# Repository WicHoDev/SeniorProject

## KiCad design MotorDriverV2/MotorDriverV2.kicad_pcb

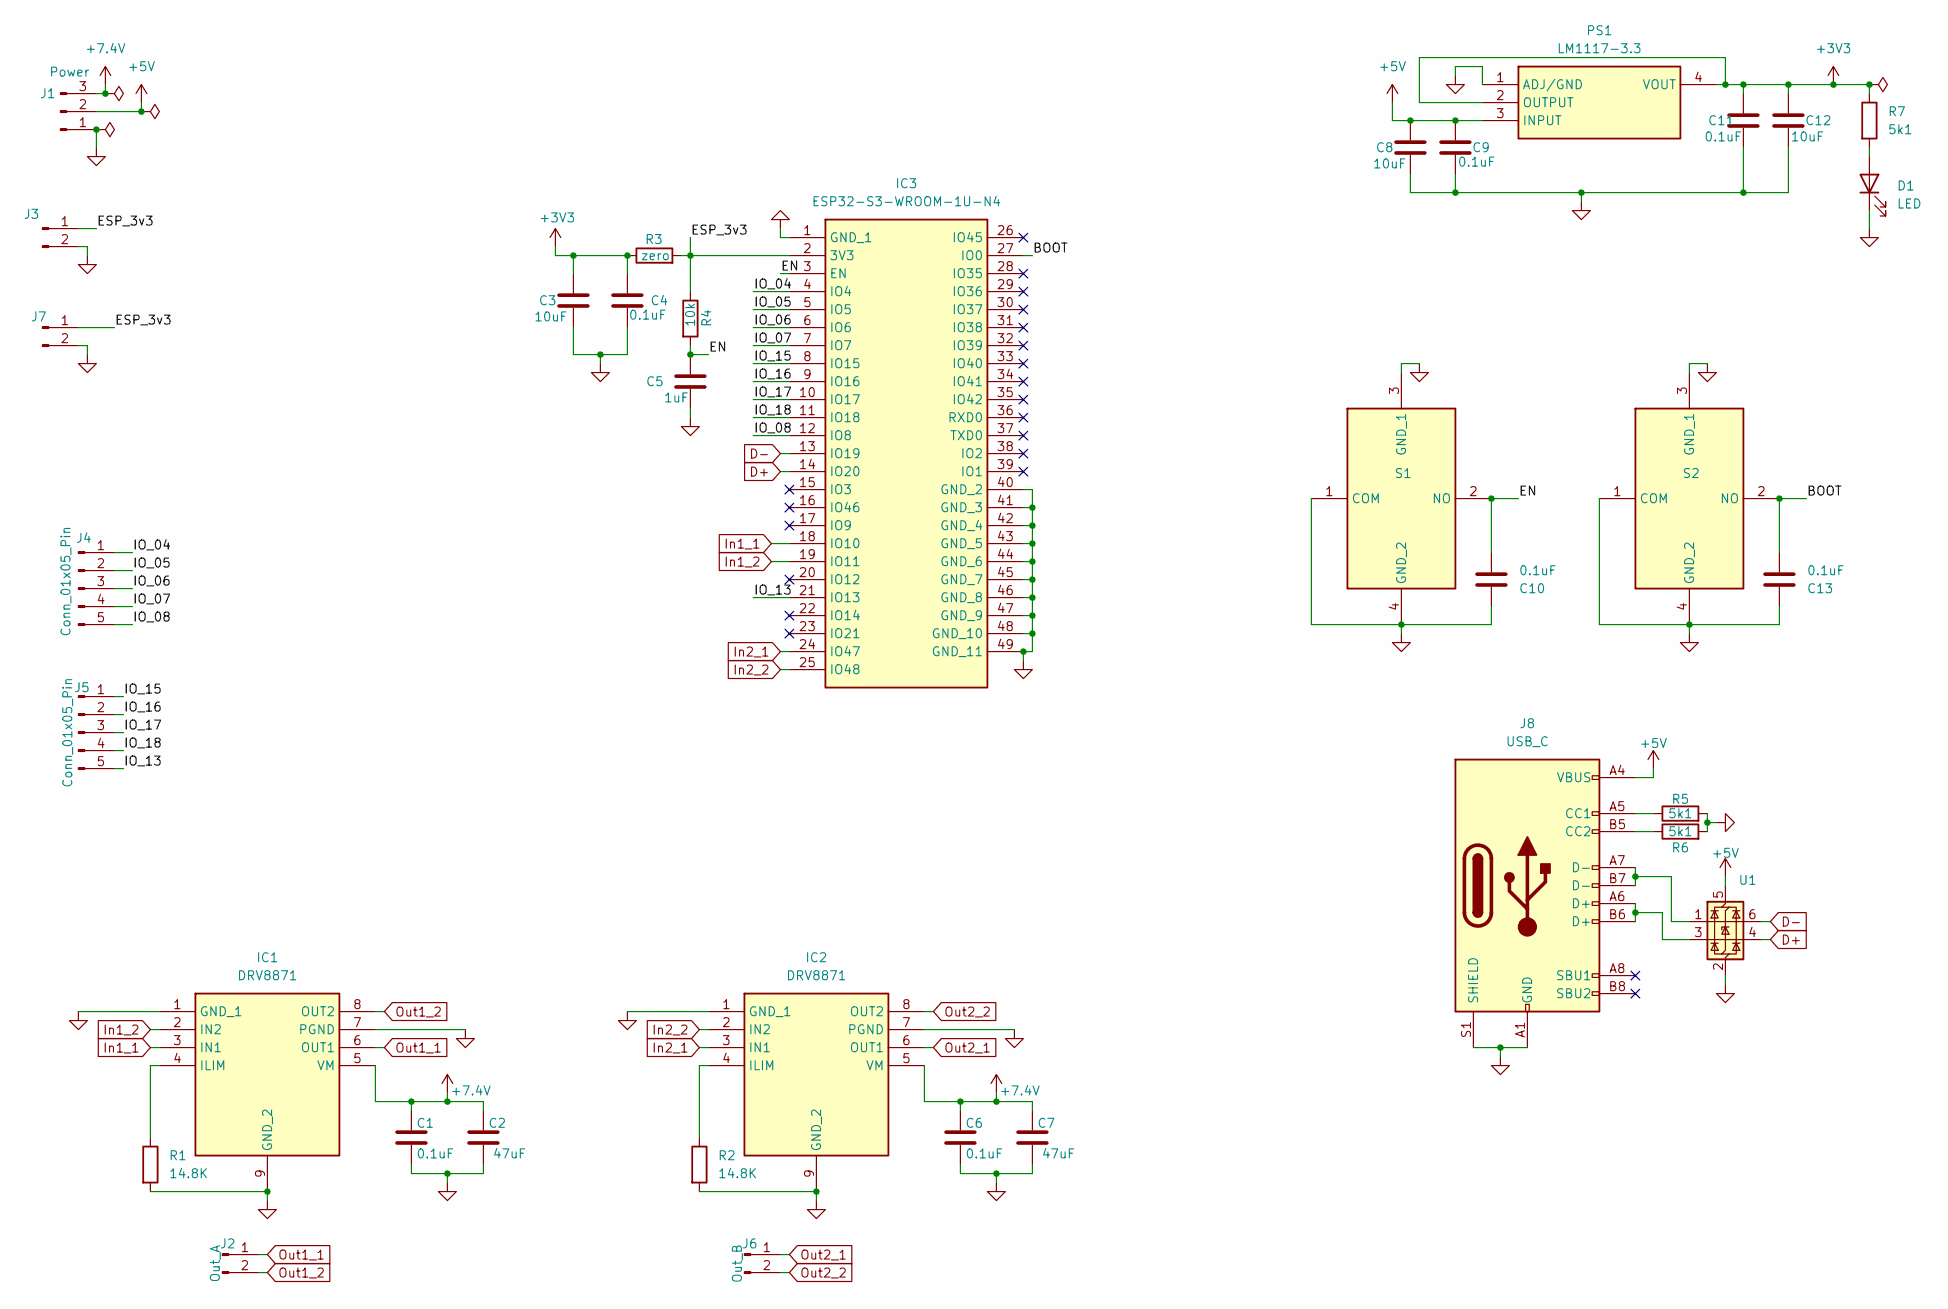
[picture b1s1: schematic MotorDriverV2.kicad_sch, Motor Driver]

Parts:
C1, C4, C6, C9, C10, C11, C13: 0.1uF; C_0805_2012Metric_Pad1.18x1.45mm_HandSolder
C2, C7: 47uF; C_0805_2012Metric_Pad1.18x1.45mm_HandSolder
C3, C8, C12: 10uF; C_0805_2012Metric_Pad1.18x1.45mm_HandSolder
C5: 1uF; C_0805_2012Metric_Pad1.18x1.45mm_HandSolder
D1: LED; LED_0805_2012Metric_Pad1.15x1.40mm_HandSolder
IC1, IC2: DRV8871; SOIC127P600X170-9N; Mouser Part Number 595-DRV8871DDARQ1
IC3: ESP32-S3-WROOM-1U-N4; ESP32S3WROOM1UN4; Mouser Part Number 356-ESP32S3WROOM1UN4
J1: Power; PinHeader_1x03_P2.00mm_Vertical
J2: Out_A; JST_XH_B2B-XH-A_1x02_P2.50mm_Vertical
J3, J7: Conn_01x02_Pin; PinHeader_1x02_P2.54mm_Vertical
J4, J5: Conn_01x05_Pin; PinHeader_1x05_P2.54mm_Vertical
J6: Out_B; JST_XH_B2B-XH-A_1x02_P2.50mm_Vertical
J8: USB_C; USB_C_Receptacle_GCT_USB4105-xx-A_16P_TopMnt_Horizontal
PS1: LM1117-3.3; SOT230P700X180-4N; Mouser Part Number 926-LM1117IMPX33NOPB
R1, R2: 14.8K; R_0805_2012Metric_Pad1.20x1.40mm_HandSolder
R3: zero; R_0805_2012Metric_Pad1.20x1.40mm_HandSolder
R4: 10k; R_0805_2012Metric_Pad1.20x1.40mm_HandSolder
R5, R6, R7: 5k1; R_0805_2012Metric_Pad1.20x1.40mm_HandSolder
S1, S2: PTS636SKG25JSMTR_LFS; PTS636SKG25JSMTRLFS; Mouser Part Number 611-PTS636SKG25JSMTR
U1: USBLC6-2SC6; SOT-23-6

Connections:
+3V3: C3.1, C4.1, C11.1, C12.1, PS1.2 (OUTPUT), PS1.4 (VOUT), R3.1, R7.1
+5V: C8.1, C9.1, J1.2, J8.A4 (VBUS), J8.A9 (VBUS), J8.B4 (VBUS), J8.B9 (VBUS), PS1.3 (INPUT), U1.5 (VBUS)
+7.4V: C1.1, C2.1, C6.1, C7.1, IC1.5 (VM), IC2.5 (VM), J1.3
/BOOT: C13.2, IC3.27 (IO0), S2.2 (NO)
/EN: C5.1, C10.2, IC3.3 (EN), R4.2, S1.2 (NO)
/ESP_3v3: IC3.2 (3V3), J3.1, J7.1, R3.2, R4.1
/IO_04: IC3.4 (IO4), J4.1
/IO_05: IC3.5 (IO5), J4.2
/IO_06: IC3.6 (IO6), J4.3
/IO_07: IC3.7 (IO7), J4.4
/IO_08: IC3.12 (IO8), J4.5
/IO_13: IC3.21 (IO13), J5.5
/IO_15: IC3.8 (IO15), J5.1
/IO_16: IC3.9 (IO16), J5.2
/IO_17: IC3.10 (IO17), J5.3
/IO_18: IC3.11 (IO18), J5.4
D+: IC3.14 (IO20), U1.4 (I/O2)
D-: IC3.13 (IO19), U1.6 (I/O1)
GND: C1.2, C2.2, C3.2, C4.2, C5.2, C6.2, C7.2, C8.2, C9.2, C10.1, C11.2, C12.2, C13.1, D1.1 (K), IC1.1 (GND_1), IC1.7 (PGND), IC1.9 (GND_2), IC2.1 (GND_1), IC2.7 (PGND), IC2.9 (GND_2), IC3.1 (GND_1), IC3.40 (GND_2), IC3.41 (GND_3), IC3.42 (GND_4), IC3.43 (GND_5), IC3.44 (GND_6), IC3.45 (GND_7), IC3.46 (GND_8), IC3.47 (GND_9), IC3.48 (GND_10), IC3.49 (GND_11), J1.1, J3.2, J7.2, J8.A1 (GND), J8.A12 (GND), J8.B1 (GND), J8.B12 (GND), J8.S1 (SHIELD), PS1.1 (ADJ/GND), R1.2, R2.2, R5.2, R6.2, S1.1 (COM), S1.3 (GND_1), S1.4 (GND_2), S2.1 (COM), S2.3 (GND_1), S2.4 (GND_2), U1.2 (GND)
In1_1: IC1.3 (IN1), IC3.18 (IO10)
In1_2: IC1.2 (IN2), IC3.19 (IO11)
In2_1: IC2.3 (IN1), IC3.24 (IO47)
In2_2: IC2.2 (IN2), IC3.25 (IO48)
unnamed: D1.2 (A), R7.2
unnamed: IC1.4 (ILIM), R1.1
unnamed: IC2.4 (ILIM), R2.1
unnamed: J8.A5 (CC1), R5.1
unnamed: J8.B5 (CC2), R6.1
unnamed: J8.A6 (D+), J8.B6 (D+), U1.3 (I/O2)
unnamed: J8.A7 (D-), J8.B7 (D-), U1.1 (I/O1)
Out1_1: IC1.6 (OUT1), J2.1
Out1_2: IC1.8 (OUT2), J2.2
Out2_1: IC2.6 (OUT1), J6.1
Out2_2: IC2.8 (OUT2), J6.2

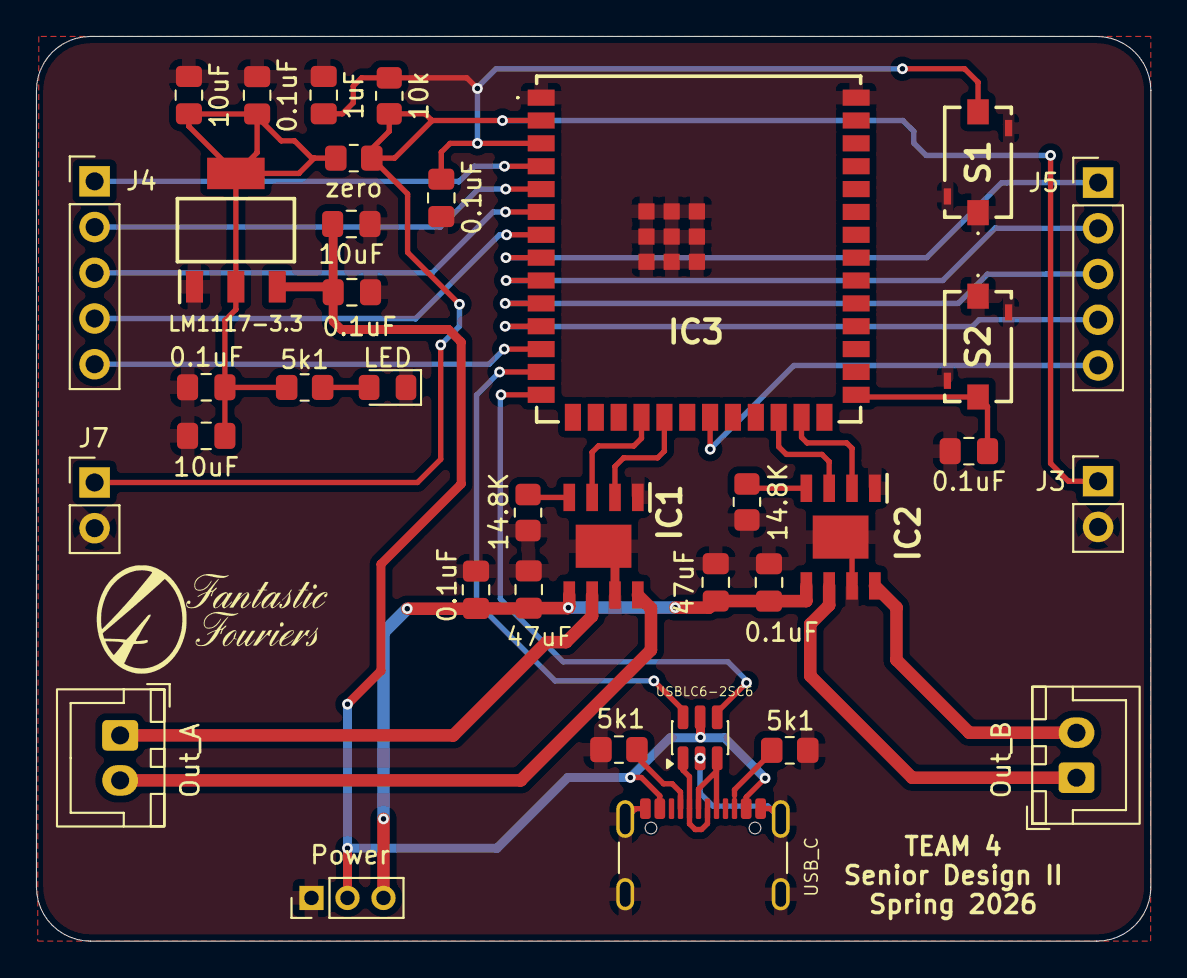
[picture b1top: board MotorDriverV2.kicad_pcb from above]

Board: 2 copper layers, 61.9 x 50.3 mm, 38 parts (1 on the bottom side), 34 nets.

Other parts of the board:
G1, G1#2: LOGO; FFLogo

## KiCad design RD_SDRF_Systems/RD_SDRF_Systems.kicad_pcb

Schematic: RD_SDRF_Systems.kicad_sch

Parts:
C1, C2, C4, C5: 0.1μF; C_0603_1608Metric
C3: 0.33μF; C_0603_1608Metric
C6, C8, C17, C22, C23: 0.01uF; C_0402_1005Metric
C7: 0.47μF; C_0603_1608Metric
C9, C11, C14: 10μF; C_0603_1608Metric
C10: 15nF; C_0603_1608Metric
C12: 10nF; C_0603_1608Metric
C13, C16, C18, C19, C20, C21: 1μF; C_0603_1608Metric
C15: 2.2nF; C_0603_1608Metric
C27, C30, C31, C32, C64, C65, C66, C67, C68, C69, C72, C73, C74, C75, C76: 0.1uF; C_0402_1005Metric
C28, C29: 10pF; C_0402_1005Metric
C33, C34, C36, C37, C81, C82: 100pF; C_0402_1005Metric
C35, C50, C54, C58: 10uF; C_0402_1005Metric
C38, C39, C40, C41, C42, C43, C45, C46, C47, C49, C51, C52, C53, C55, C56, C57, C59, C79, C80: 100nF; C_0402_1005Metric
C44: 2.2uF; C_0402_1005Metric
C48: 1uF; C_0402_1005Metric
C60, C61: 20pF; C_0402_1005Metric
C62, C71: 18pF; C_0402_1005Metric
C63, C70: 4.7uF; C_0402_1005Metric
C77, C78: 10uF; CP_EIA-3528-21_Kemet-B
FB1, FB2, FB3, FB4, FB6, FB7: FerriteBead_Small; L_0402_1005Metric
IC1: ERA-50SM+; ERA50SM; Mouser Part Number 139-ERA-50SM
J1, J2: 132255-11; CONN_132255-11_AMP
J3: FTSH-105-01-L-DV-K; CON10_2X5_DUK_FTSH_SAI
J4: USB_C_Receptacle_USB2.0_16P; USB_C_Receptacle_GCT_USB4105-xx-A_16P_TopMnt_Horizontal
J5: Conn_01x02_Pin; PinHeader_1x02_P2.54mm_Vertical
R1, R2, R3, R4: 10kΩ; R_0402_1005Metric
R5: 330; R_0402_1005Metric
R6, R10: 50; R_0402_1005Metric
R7, R8, R11, R12: 0; R_0402_1005Metric
R9: 30k; R_0402_1005Metric
R13, R14, R15: 10k; R_0402_1005Metric
R16, R17, R21, R22: 100; R_0402_1005Metric
R18: 10; R_0402_1005Metric
R19, R20, R23, R24, R25, R26: 10000; R_0402_1005Metric
R27, R28: 5100; R_0402_1005Metric
R29: 100k; R_0402_1005Metric
R30: 200k; R_0402_1005Metric
R31: 12000; R_0402_1005Metric
R32: 22; R_0402_1005Metric
TR1: TC1-1-13M+; Transformer_MiniCircuits_AT224-1A
U1: LMX2572LPRHAT; IC_LMX2572LPRHAT; PARTREV 08/22/2019
U2: TRF371109IRGZT; RGZ48_5P6X5P6
U3: AD4630-16BBCZ; 05-08-1797_ADI
U4, U5: SN74AXC8T245PWR; PW0024A_N
U6: STM32H723ZGT6; QFP50P2200X2200X160-144N; PARTREV 4
U7: USB3300-EZK-TR; QFN50P500X500X100-33N; DIGI-KEY_PART_NUMBER USB3300-EZK-CT-ND
U8, U9: LM1117MP-1.8; SOT230P700X180-4N
VR1: UA78M33CDCYR; VREG_UA78M33CDCYR; PARTREV T
X1: AK2PAF1-100.00000T; AK2_ABR
Y1: ABM8-25.000MHZ-B2-T; XTAL_ABM8-25.000MHZ-B2-T; PARTREV 44041
Y2: ABM8-24.000MHz-10-B1U-T; XTAL_ABM8-24.000MHz-10-B1U-T; PARTREV 44041

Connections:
+5V: C3.1, C30.2, C31.2, FB1.1, FB2.1, FB3.1, FB4.1, FB7.1, J5.1, R13.1, R14.1, R15.1, R18.1, U2.4 (VCCMIX1), U2.9 (VCCMIX2), U3.A3 (VDD_5V), U3.B3 (VDD_5V), VR1.1 (INPUT)
/1V8: C39.1, C41.1, C63.1, C66.1, C68.1, C70.1, C76.1, C78.2, R19.1, R20.1, U2.24 (VCM), U3.A8 (VIO), U3.B8 (VIO), U3.G3 (VDD_1.8V), U3.H3 (VDD_1.8V), U4.1 (VCCA), U4.2 (DIR), U4.11 (DIR2), U5.1 (VCCA), U7.15 (VDD1.8-1), U7.26 (VDD1.8), U7.29 (VDDA1.8), U9.2 (VOUT__1), U9.4 (VOUT)
/*CS: R20.2, U3.H5 (*CS), U4.5 (A3)
/*RST: R19.2, U3.A7 (*RST), U4.7 (A5)
/AD4630_BUSY: U5.21 (B1), U6.49 (PF11)
/AD4630_CNV: U4.18 (B4), U6.65 (PE12)
/AD4630_CS: U4.19 (B3), U6.64 (PE11)
/AD4630_RST: U4.17 (B5), U6.66 (PE13)
/AD4630_SDO0: U5.20 (B2), U6.50 (PF12)
/AD4630_SDO1: U5.19 (B3), U6.53 (PF13)
/AD4630_SDO2: U5.18 (B4), U6.54 (PF14)
/AD4630_SDO3: U5.17 (B5), U6.55 (PF15)
/BUSY: U3.E8 (BUSY_SCKOUT), U5.3 (A1)
/CNV: U3.A6 (CNV), U4.6 (A4)
/DM: J4.A7 (D-), J4.B7 (D-), U7.8 (DM)
/DP: J4.A6 (D+), J4.B6 (D+), U7.7 (DP)
/I_Channel+: R16.1, U2.34 (BBLOUTP)
/I_Channel-: R17.1, U2.33 (BBLOUTN)
/LMX_CE: U1.1 (CE), U6.4 (PE5)
/LMX_CSB: U1.24 (CSB), U6.35 (PA1)
/LOIN: C6.2, U2.30 (LOIN)
/LOIP: C8.2, U2.31 (LOIP)
/MIXINN: C29.2, U2.7 (MIXINN)
/MIXINP: C28.2, U2.6 (MIXINP)
/OSCINM: C1.1, U1.9 (OSCINM)
/OSCINP: C2.1, U1.8 (OSCINP)
/Q_Channel+: R22.2, U2.28 (BBQOUTP)
/Q_Channel-: R21.2, U2.27 (BBQOUTN)
/RF_MIXIN: C23.1, TR1.6
/RF_MUXout: U1.20 (MUXOUT), U6.36 (PA2)
/SCK: U3.H7 (SCK), U4.3 (A1)
/SDI: U3.H6 (SDI), U4.4 (A2)
/SDO0: U3.D8 (SDO0), U5.7 (A5)
/SDO1: U3.C8 (SDO1), U5.6 (A4)
/SDO2: U3.D7 (SDO2), U5.5 (A3)
/SDO3: U3.C7 (SDO3), U5.4 (A2)
/SPI1_MISO: U6.43 (PA7)
/SPI1_MOSI: U1.17 (SDI), U2.47 (DATA), U4.20 (B2), U6.42 (PA6)
/SPI1_SCK: R32.2, U1.16 (SCK), U2.48 (CLOCK), U4.21 (B1)
/SWO: J3.6, U6.133 (PB3/JTDO/TRACESWO)
/TRF_EN: U2.3 (CHIP_EN), U6.45 (PC5)
/TRF_STROBE: U2.46 (STROBE), U6.40 (PA4)
/ULPI_CLK: U6.100 (PA8), U7.14 (CLKOUT)
/ULPI_D0: U6.37 (PA3), U7.24 (DATA[0])
/ULPI_D1: U6.46 (PB0), U7.23 (DATA[1])
/ULPI_D2: U6.47 (PB1), U7.22 (DATA[2])
/ULPI_D3: U6.69 (PB10), U7.21 (DATA[3])
/ULPI_D4: U6.70 (PB11), U7.20 (DATA[4])
/ULPI_D5: U6.73 (PB12), U7.19 (DATA[5])
/ULPI_D6: U6.74 (PB13), U7.18 (DATA[6])
/ULPI_D7: U6.135 (PB5), U7.17 (DATA[7])
/ULPI_DIR: U6.28 (PC2_C), U7.12 (DIR)
/ULPI_NXT: U6.29 (PC3_C), U7.11 (NXT)
/ULPI_RST: U6.44 (PC4), U7.9 (RESET)
/ULPI_STP: U6.26 (PC0), U7.13 (STP)
/VBUS: J4.A4 (VBUS), J4.A9 (VBUS), J4.B4 (VBUS), J4.B9 (VBUS), R29.2
/nRST: C42.1, J3.8, R23.2, U6.25 (~RST)
unnamed: C10.2, R5.1
unnamed: C17.2, J1.1
unnamed: C22.2, J2.1
unnamed: C28.1, TR1.1
unnamed: C29.1, TR1.3
unnamed: C62.1, Y2.1
unnamed: C23.2, IC1.3 (RF-OUT_AND_DC-IN)
unnamed: C22.1, IC1.1 (RFIN)
unnamed: J4.A5 (CC1), R27.1
unnamed: J4.B5 (CC2), R28.1
unnamed: R10.1, TR1.4
unnamed: R2.1, U1.30 (RAMPCLK)
unnamed: R3.1, U1.32 (RAMPDIR)
unnamed: R6.1, U1.22 (RFOUTAM)
unnamed: C17.1, U1.23 (RFOUTAP)
unnamed: C8.1, U1.18 (RFOUTBM)
unnamed: C6.1, U1.19 (RFOUTBP)
unnamed: R1.1, U1.5 (SYNC)
unnamed: R4.1, U1.28 (SYSREFREQ)
unnamed: C9.1, U1.33 (VBIASVARAC)
unnamed: C5.1, U1.27 (VBIASVCO2)
unnamed: C7.1, U1.3 (VBIASVCO)
unnamed: C11.1, U1.29 (VREFVCO2)
unnamed: C14.1, U1.36 (VREFVCO)
unnamed: C13.1, U1.10 (VREGIN)
unnamed: C12.1, U1.38 (VREGVCO)
unnamed: R13.2, U2.41 (GAIN_B0)
unnamed: R14.2, U2.40 (GAIN_B1)
unnamed: R15.2, U2.39 (GAIN_B2)
unnamed: R12.2, U2.44 (MIXIOUTN)
unnamed: R11.2, U2.45 (MIXOUTP)
unnamed: R8.2, U2.17 (MIXQOUTN)
unnamed: R7.2, U2.16 (MIXQOUTP)
unnamed: R9.2, U2.20 (REXT)
unnamed: C75.1, FB4.2, U2.36 (VCBBI)
unnamed: C73.1, FB2.2, U2.25 (VCCBBQ)
unnamed: C72.1, FB7.2, U2.21 (VCCBIAS)
unnamed: C27.1, FB1.2, U2.2 (VCCDIG)
unnamed: C74.1, FB3.2, U2.29 (VCCLO)
unnamed: C33.1, C81.2, R16.2, U3.B1 (IN0+)
unnamed: C34.1, C81.1, R17.2, U3.C1 (IN0-)
unnamed: C37.1, C82.2, R22.1, U3.F1 (IN1+)
unnamed: C36.1, C82.1, R21.1, U3.G1 (IN1-)
unnamed: C35.1, R18.2, U3.A2 (REFIN)
unnamed: R24.2, U6.138 (BOOT0)
unnamed: R32.1, U6.41 (PA5)
unnamed: J3.2, R25.2, U6.105 (PA13/JTMS/SWDIO)
unnamed: J3.4, R26.1, U6.109 (PA14/JTCK/SWCLK)
unnamed: C47.1, C48.2, FB6.1, U6.32 (VREF+)
unnamed: C60.2, U6.23 (PH0-OSC_IN), Y1.1
unnamed: C61.2, U6.24 (PH1-OSC_OUT), Y1.3
unnamed: R31.1, U7.32 (RBIAS)
unnamed: R29.1, R30.1, U7.4 (VBUS)
unnamed: C62.2, U7.28 (XI)
unnamed: C71.1, U7.27 (XO), Y2.3
unnamed: C1.2, X1.5 (COMPLEMENTARY_OUTPUT)
unnamed: C2.2, X1.4 (OUTPUT)
VCAP: C44.1, U6.71 (VCAP), U6.106 (VCAP)
VCC: C4.1, C16.1, C18.1, C19.1, C20.1, C21.1, C32.2, C38.1, C40.1, C43.2, C45.2, C46.1, C49.2, C50.2, C51.2, C52.1, C53.1, C54.2, C55.2, C56.1, C57.2, C58.2, C59.2, C64.1, C65.1, C67.1, C69.1, C77.1, C79.2, C80.2, FB6.2, J3.1, R23.1, R25.1, U1.7 (VCCDIG), U1.11 (VCCCP), U1.15 (VCCMASH), U1.26 (VCCVCO2), U1.37 (VCCVCO), U4.23 (VCCB), U5.23 (VCCB), U6.6 (VBAT), U6.17 (VDD), U6.30 (VDD), U6.33 (VDDA), U6.39 (VDD), U6.52 (VDD), U6.62 (VDD), U6.72 (VDD), U6.84 (VDD), U6.95 (VDD33USB), U6.108 (VDD), U6.121 (VDD), U6.131 (VDD), U6.143 (PDR_ON), U6.144 (VDD), U7.5 (ID), U7.6 (VDD3.3-3), U7.16 (VDD3.3-2), U7.25 (VDD3.3-1), U7.30 (VDD3.3), U7.31 (REG_EN), U9.3 (VIN), VR1.3 (OUTPUT)

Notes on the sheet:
RF Synthesizer
Oscillator_RF Synth
Analog-to-Digital Converter
Low Noise Amplifier
Level Shifters
USB-C
Balun
Voltage Regulator
10uF capacitors are found https://www.digikey.com/en/models/818691?tab=ultralibrarian
Loop Filter
Down Converter
STM32 MCU

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
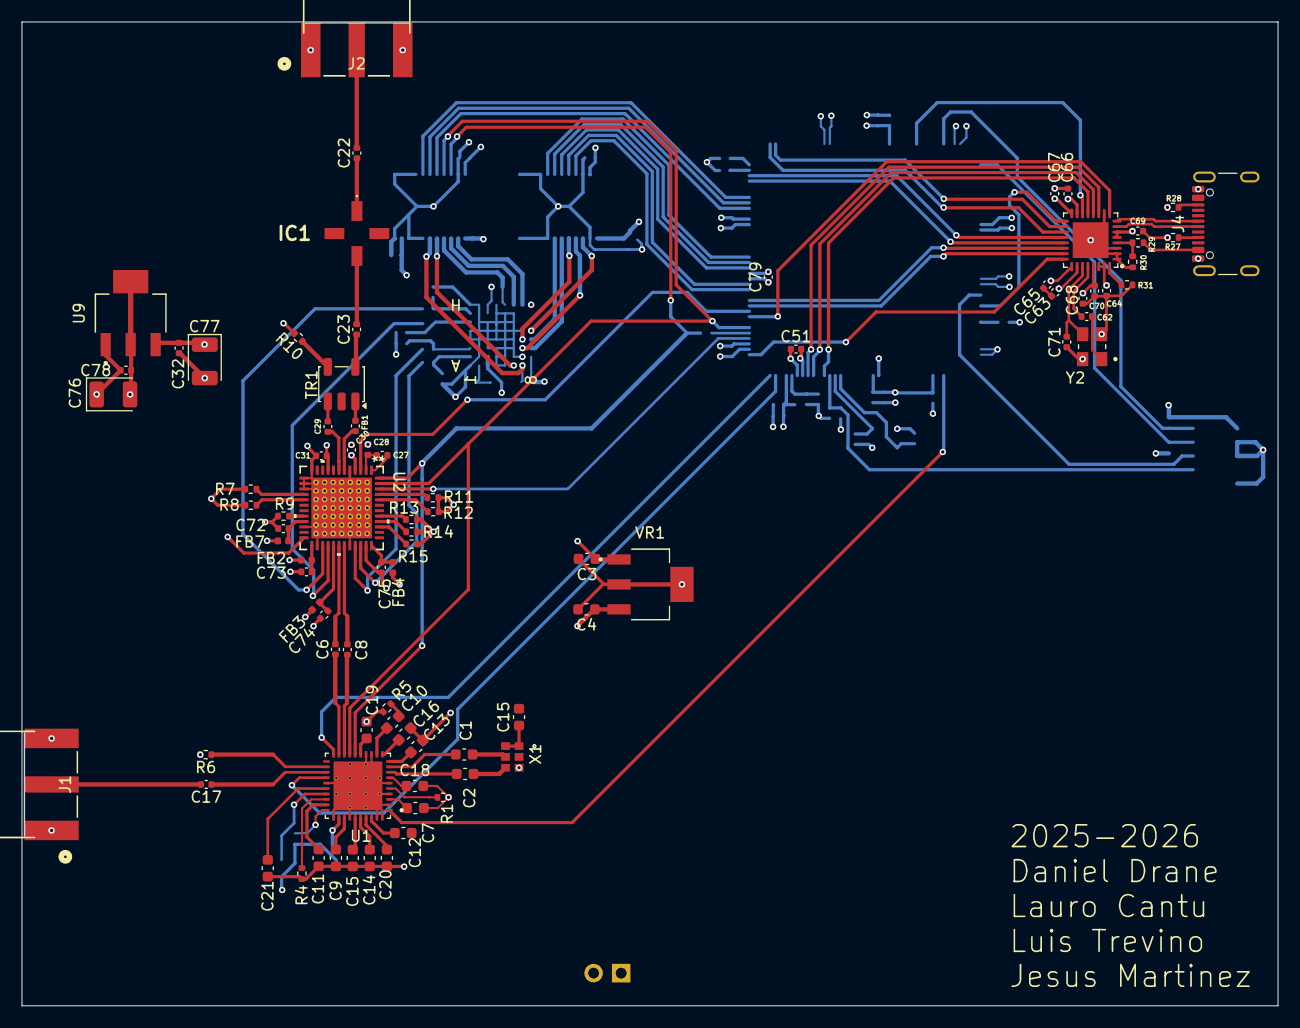
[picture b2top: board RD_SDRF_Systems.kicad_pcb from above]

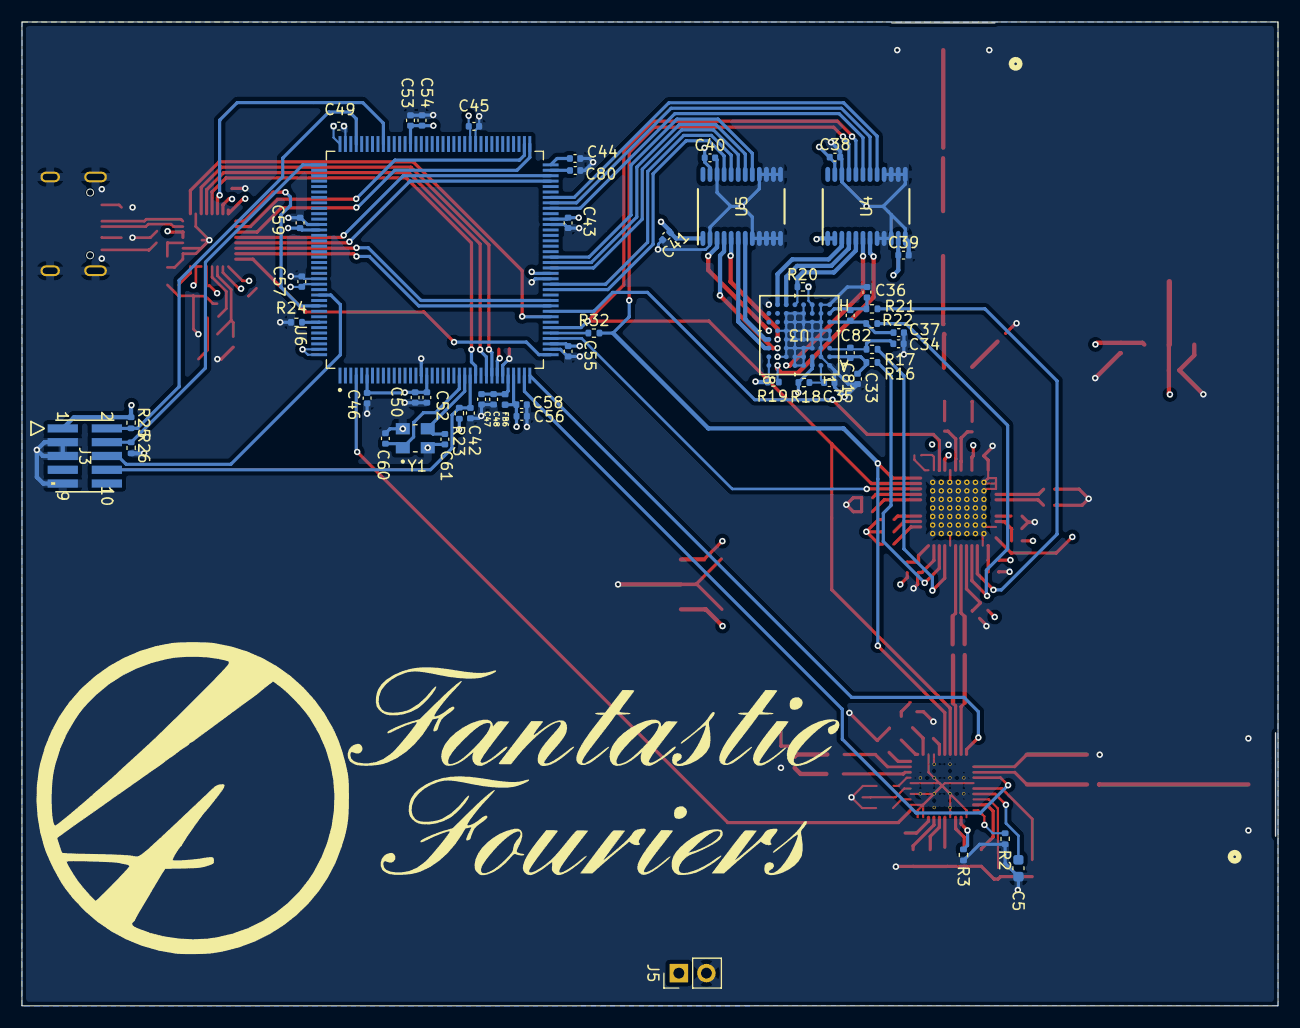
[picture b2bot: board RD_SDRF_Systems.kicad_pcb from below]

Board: 4 copper layers, 115.7 x 90.6 mm, 137 parts (54 on the bottom side), 118 nets.

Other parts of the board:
C15#2: 2.2nF; C_0603_1608Metric

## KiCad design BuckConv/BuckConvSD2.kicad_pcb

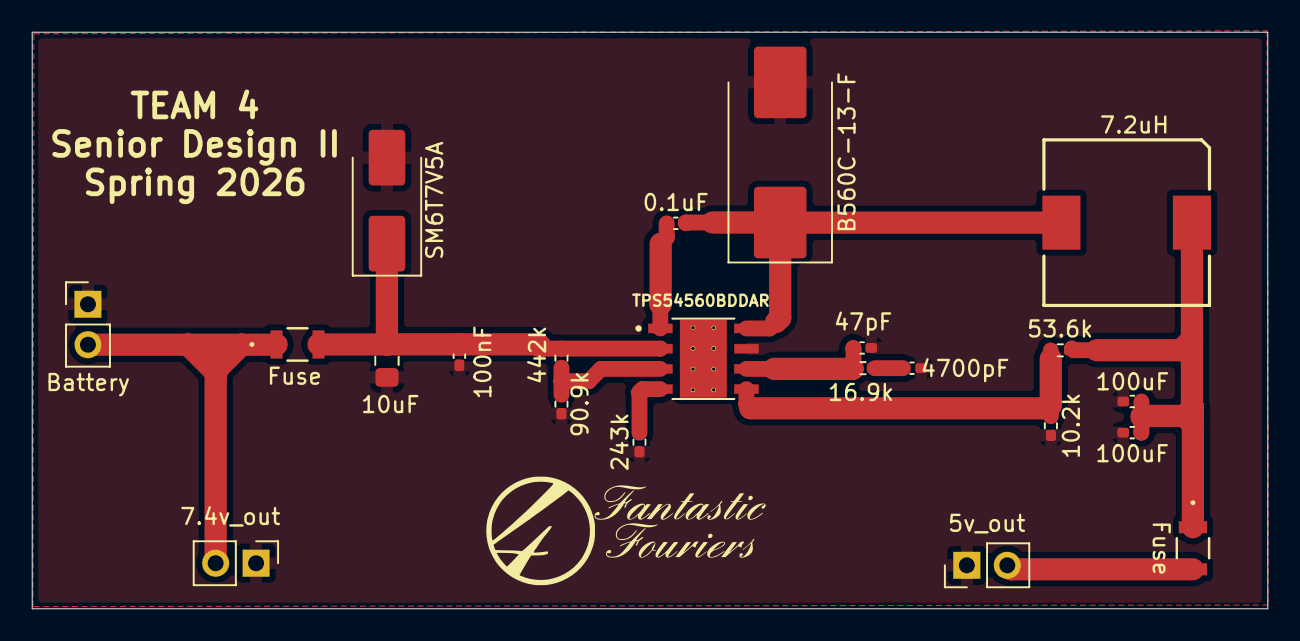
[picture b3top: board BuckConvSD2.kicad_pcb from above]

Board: 2 copper layers, 77.6 x 36.2 mm, 22 parts (0 on the bottom side), 12 nets.

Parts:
C1: 10uF; C_0805_2012Metric_Pad1.18x1.45mm_HandSolder
C2: 100nF; C_0402_1005Metric_Pad0.74x0.62mm_HandSolder
C3: 0.1uF; C_0402_1005Metric_Pad0.74x0.62mm_HandSolder
C4: 4700pF; C_0402_1005Metric_Pad0.74x0.62mm_HandSolder
C5: 47pF; C_0402_1005Metric_Pad0.74x0.62mm_HandSolder
C6, C7: 100uF; C_0402_1005Metric_Pad0.74x0.62mm_HandSolder
CR1: B560C-13-F; D_SMC_Handsoldering
D1: SM6T7V5A; D_SMB_Handsoldering
F1, F2: Fuse; FUSE_0685T5000-01_BEL
J2: 5v_out; PinHeader_1x02_P2.54mm_Vertical
J3: Battery; PinHeader_1x02_P2.54mm_Vertical
J4: 7.4v_out; PinHeader_1x02_P2.54mm_Vertical
L1: 7.2uH; WE-PDF_1064
R1: 442k; R_0402_1005Metric_Pad0.72x0.64mm_HandSolder
R2: 90.9k; R_0402_1005Metric_Pad0.72x0.64mm_HandSolder
R3: 243k; R_0402_1005Metric_Pad0.72x0.64mm_HandSolder
R4: 16.9k; R_0402_1005Metric_Pad0.72x0.64mm_HandSolder
R5: 53.6k; R_0402_1005Metric_Pad0.72x0.64mm_HandSolder
R6: 10.2k; R_0402_1005Metric_Pad0.72x0.64mm_HandSolder
U1: TPS54560BDDAR; VREG_LM5017MR_NOPB

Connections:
/7v4: F1.1, J3.2, J4.2
/FB: R5.1, R6.2, U1.5 (FB)
GND: C1.1, C2.1, C4.1, C5.1, C6.1, C7.2, CR1.2, D1.2 (A2), J2.1, J3.1, J4.1, R2.1, R3.1, R6.1, U1.7 (GND)
unnamed: C4.2, R4.1
unnamed: C6.2, C7.1, F2.1, L1.2, R5.2
unnamed: C1.2, C2.2, D1.1 (A1), F1.2, R1.1, U1.2 (VIN)
unnamed: F2.2, J2.2
unnamed: C3.1, U1.1 (BOOT)
unnamed: C5.2, R4.2, U1.6 (COMP)
unnamed: R1.2, R2.2, U1.3 (EN)
unnamed: R3.2, U1.4 (RT/CLK)
unnamed: C3.2, CR1.1, L1.1, U1.8 (SW)

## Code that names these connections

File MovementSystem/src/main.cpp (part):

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 *
 *  Pi GPIO  │ ESP32 Pin │ Signal   │ Description
 *  ─────────┼───────────┼──────────┼───────────────────────────────
 *  IO_04    │ GPIO4     │ ENABLE   │ HIGH = motors active, LOW = stop (coast)
 *  IO_05    │ GPIO5     │ DIR_L    │ HIGH = left motor forward, LOW = reverse
 *  IO_06    │ GPIO6     │ DIR_R    │ HIGH = right motor forward, LOW = reverse
 *  IO_07    │ GPIO7     │ SPD_S0   │ Speed bit 0 (LSB)
 *  IO_08    │ GPIO8     │ SPD_S1   │ Speed bit 1
 *  IO_15    │ GPIO15    │ SPD_S2   │ Speed bit 2 (MSB)
 *
 *  Speed encoding (S2 S1 S0):
 *    000 →   0% PWM duty  (stopped, but ENABLE still high → brake mode)
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// ═══════════════════════════════════════════════════════════
//  PI → ESP32 INPUT PINS  (bit-bang interface)
// ═══════════════════════════════════════════════════════════
#define PIN_ENABLE   4    // IO_04 — global enable
#define PIN_DIR_L    5    // IO_05 — left  motor direction
#define PIN_DIR_R    6    // IO_06 — right motor direction
#define PIN_SPD_S0   7    // IO_07 — speed bit 0 (LSB)
#define PIN_SPD_S1   8    // IO_08 — speed bit 1
#define PIN_SPD_S2   15   // IO_15 — speed bit 2 (MSB)

// ═══════════════════════════════════════════════════════════
//  ESP32 → DRV8871 OUTPUT PINS  (per schematic)
// ═══════════════════════════════════════════════════════════
#define PIN_L_IN1    10   // IO10 — Left  motor DRV8871 IN1  (In1_1)
#define PIN_L_IN2    11   // IO11 — Left  motor DRV8871 IN2  (In1_2)
#define PIN_R_IN1    47   // IO47 — Right motor DRV8871 IN1  (In2_1)
#define PIN_R_IN2    48   // IO48 — Right motor DRV8871 IN2  (In2_2)

// ═══════════════════════════════════════════════════════════
//  LEDC PWM CONFIG
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
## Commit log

2025-10-14 test commit
2025-10-17 starting Data Link protocol
2025-10-18 Create simple TCP
2025-11-17 client update
2025-11-17 implemented fake data transfer
2025-11-18 UPDATE: created new file structure
2025-11-20 ADD: require libraries for project
2025-11-20 UPDATE: working code - receiveng data
2025-11-20 UPDATE: require libraries
2025-12-03 Getting ScreenShoots for report xD
2025-12-03 TEST01: simple TCP connection
2025-12-04 TEST02: 'Fake' data transfer
2025-12-09 ADD: movement control
2025-12-10 UPDATE: working movemnt controll
2025-12-10 UPDATE: for final test
2025-12-10 ADD: git ignore
2025-12-10 UPDATE: add git ignore, and python libs
2025-12-11 UPDATE: receiving Data store in file
2025-12-11 UPDATE: ignored files
2025-12-11 UPDATE: Server files
2025-12-11 UPDATE: Receiving Data
2025-12-11 UPDATE: Working client, receiving data
2025-12-11 UPDATE: Enable reconnectivity
2025-12-12 UPDATE: Working Movement Control
2025-12-12 UPDATE: port to esp32
2026-01-23 UPDATE REPO | Jan-23-2026
2026-01-27 Create Senior Design II branch
2026-02-05 UPDATE: test movement
2026-02-19 ADDED: Controll PCB
2026-02-25 UPDATE: Added symbols, fotprints and datasheets for components
2026-02-25 UPDATE: Added symbols, fotprints and datasheets for components, third time xD
2026-03-08 UPDATE: Schematic
2026-03-08 UPDATE: Symbols and footprint added, need to finish layout
2026-03-31 Final Update
2026-04-11 Completed PCB's
2026-04-11 completed pcb
2026-04-13 TEST: Website
2026-04-16 UPDATE: website
2026-04-17 UPDATE: Fix EN pin in ESP motor driver
2026-04-24 UPDATE: layout
2026-04-28 UPDATE: Change MoveSys files
2026-05-02 UPDATE: PI and ESP32 communication working
2026-05-02 UPDATE: Working website
